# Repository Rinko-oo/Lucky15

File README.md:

# Lucky15
15 key + rotary encoder macropad for media control and macros

## CAD

## PCB

## Schematic

## BOM
This is everything needed to build the Lucky15, currently all available on AliExpress\
**NOTE** - Welcome deal was applied to the Milky Yellow switches
| Qty | Part | Link | Cost (CAD) |
| --- | ---- | ---- | ---------- |
| 1 | NRF52840 | [Link](https://www.aliexpress.com/item/1005007205026373.html) | $6.09 |
| 15 | Gateron Milky Yellow Switches | [Link](https://www.aliexpress.com/item/1005007039372956.html) | $1.41 |
| 1 | Polymer Lithium Battery 600mAh | [Link](https://www.aliexpress.com/item/1005007905669396.html) | $11.58 |
| 1 | 0.91 Inch OLED Display | [Link](https://www.aliexpress.com/item/1005008640108394.html) | $3.54 |
| 16 | 1N4148 Diodes | [Link](https://www.aliexpress.com/item/1005009379098965.html) | $4.29 |
| 2 | 2.54mm Silver Headers | [Link](https://www.aliexpress.com/item/4001122376295.html) | $3.79 |
| 15 | Blank Keycaps | [Link](https://www.aliexpress.com/item/1005007683242914.html) | $8.79 |
| 1 | EC11 Rotary Encoder | [Link](https://www.aliexpress.com/item/1005004908084537.html) | $6.24 |
| 1 | PCB | [Link](https://jlcpcb.com/) | $11.18 |
| 1 | MSK12C02 Switch | [Link](https://www.aliexpress.com/item/4000685483225.html) | $3.59 |
|  |  | **Total** | **$60.50** |

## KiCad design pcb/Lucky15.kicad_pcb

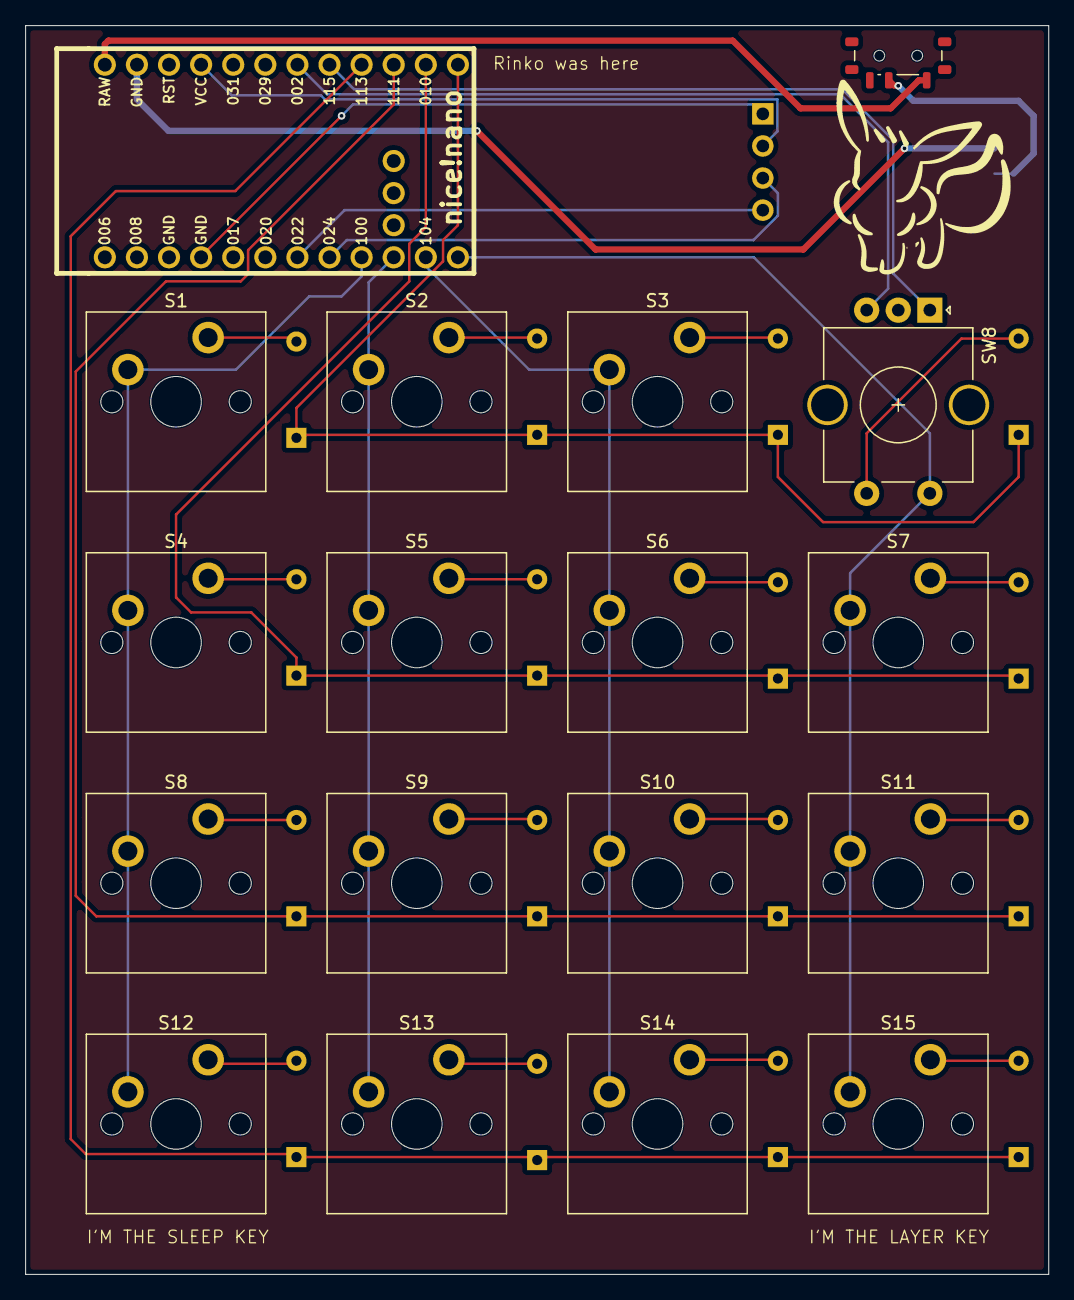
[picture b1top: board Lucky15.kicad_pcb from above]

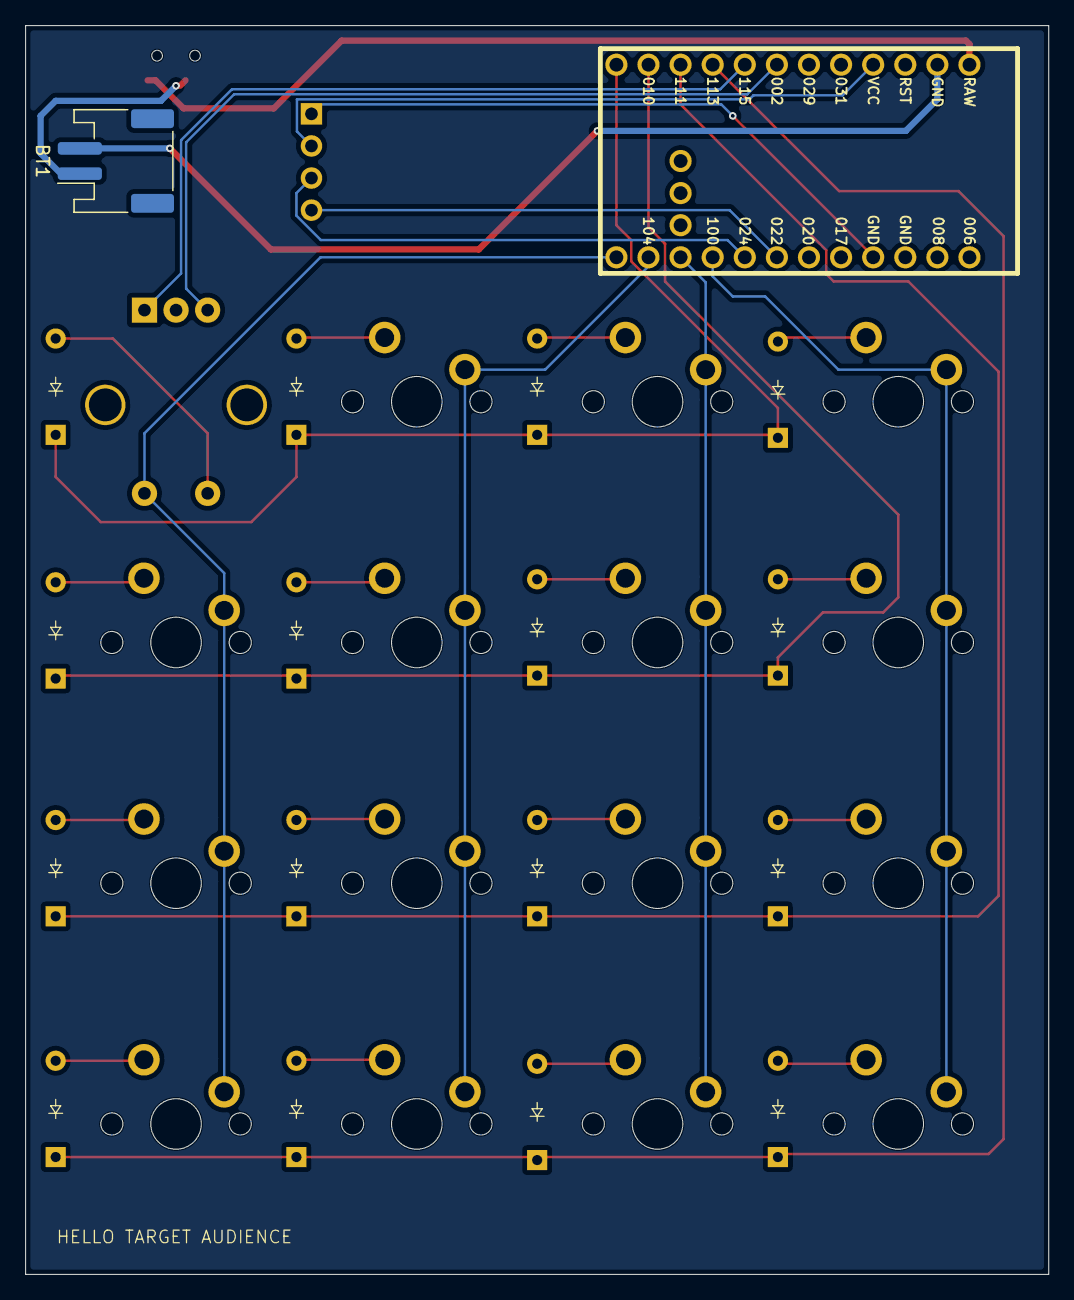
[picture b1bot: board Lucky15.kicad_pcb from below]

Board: 2 copper layers, 81.0 x 98.8 mm, 36 parts (17 on the bottom side), 33 nets.

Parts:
BT1: Battery; JST_PH_S2B-PH-SM4-TB_1x02-1MP_P2.00mm_Horizontal
D1, D2, D3, D4, D5, D6, D7, D8, D9, D10, D11, D12, D13, D14, D15, D16: Diode_DO-35
J1: OLED_128x32
S1, S2, S3, S4, S5, S6, S7, S8, S9, S10, S11, S12, S13, S14, S15: MX_PCB_1.00u
SW1: SW_SPDT; SW_SPDT_Shouhan_MSK12C02
SW8: RotaryEncoder_Switch; RotaryEncoder_Alps_EC11E-Switch_Vertical_H20mm_CircularMoun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
U1: ProMicro; nice_nano

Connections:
BATT+: SW1.1 (A), U1.24 (RAW)
BATT-: BT1.2 (-), U1.23 (GND)
Column 0: S1.1, S4.1, S8.1, S12.1, U1.9 (6/D7)
Column 1: S2.1, S5.1, S9.1, S13.1, U1.10 (7/E6)
Column 2: S3.1, S6.1, S10.1, S14.1, U1.11 (8/B4)
Column 3: S7.1, S11.1, S15.1, SW8.S2, U1.12 (9/B5)
ENCO_A: SW8.A, U1.17 (F7/A0)
ENCO_B: SW8.B, U1.18 (F6/A1)
unnamed: BT1.1 (+), SW1.2 (B)
unnamed: D1.2 (A), S1.2
unnamed: D2.2 (A), S2.2
unnamed: D3.2 (A), S3.2
unnamed: D4.2 (A), S4.2
unnamed: D5.2 (A), S5.2
unnamed: D6.2 (A), S6.2
unnamed: D7.2 (A), S7.2
unnamed: D8.2 (A), S8.2
unnamed: D9.2 (A), S9.2
unnamed: D10.2 (A), S10.2
unnamed: D11.2 (A), S11.2
unnamed: D12.2 (A), S12.2
unnamed: D13.2 (A), S13.2
unnamed: D14.2 (A), S14.2
unnamed: D15.2 (A), S15.2
unnamed: D16.2 (A), SW8.S1
OLED_GND: J1.1 (GND), U1.4 (GND)
OLED_SCL: J1.3 (SCL), U1.8 (5/C6)
OLED_SDA: J1.4 (SDA), U1.7 (4/D4)
OLED_VCC: J1.2 (VCC), U1.21 (VCC)
Row 0: D1.1 (K), D2.1 (K), D3.1 (K), D16.1 (K), U1.13 (B6/10)
Row 1: D4.1 (K), D5.1 (K), D6.1 (K), D7.1 (K), U1.14 (B2/16)
Row 2: D8.1 (K), D9.1 (K), D10.1 (K), D11.1 (K), U1.15 (B3/14)
Row 3: D12.1 (K), D13.1 (K), D14.1 (K), D15.1 (K), U1.16 (B1/15)

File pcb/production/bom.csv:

Designator,Footprint,Quantity,Value,LCSC Part #
BT1,JST_PH_S2B-PH-SM4-TB_1x02-1MP_P2.00mm_Horizontal,1,Battery,
"D1, D10, D11, D12, D13, D14, D15, D16, D2, D3, D4, D5, D6, D7, D8, D9",Diode_DO-35,16,~,
J1,OLED_128x32,1,OLED_128x32,
"S1, S10, S11, S12, S13, S14, S15, S2, S3, S4, S5, S6, S7, S8, S9",MX_PCB_1.00u,15,~,
SW8,RotaryEncoder_Alps_EC11E-Switch_Vertical_H20mm_CircularMountingHoles,1,RotaryEncoder_Switch,
U1,nice_nano,1,ProMicro,
